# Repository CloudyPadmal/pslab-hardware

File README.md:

# pslab-hardware

This repository contains the [PSLab](https://pslab.io) hardware design files. PSLab is a tiny pocket science lab that provides an array of test and measurement instruments for doing science and engineering experiments. It can function like an oscilloscope, waveform generator, frequency counter, programmable voltage and current source and also as a data logger. The first version of hardware (v1) was developed by [Jithin B P](https://github.com/jithinbp). Later versions were developed by [Padmal](https://github.com/CloudyPadmal).

## PCB Layout
Front Side                        | Back Side
 -------------------------------- | ----------------------------------
 | 

## Pin-outs
- Find the pin-out diagram of PSLab v6 [here](docs/pin_layouts/PSLab_Pin_Layout.pdf)!

## Applications and Firmware Source Repositories

| 	|	| 	| 	| 	|
|---	|---	|---	|---	|---	|

The following software components are available:
* Firmware: https://github.com/fossasia/pslab-firmware
* Android app: https://github.com/fossasia/pslab-android
* Desktop app: https://github.com/fossasia/pslab-desktop

## Buy Device

* You can get a Pocket Science Lab device from the [FOSSASIA Shop](https://fossasia.com).
* More resellers are listed on the [PSLab website](https://pslab.io/shop/).

## Communication

* Our chat channel is on Gitter here at [PSLab](https://gitter.im/fossasia/pslab)
* Mailing List https://groups.google.com/forum/#!forum/pslab-fossasia

## Repository Structure

```
📦pslab-hardware
 ┣ 📂archives                                   # Source files for previous PSLab versions
 ┃ ┣ 📂Breakout_Boards
 ┃ ┣ 📂PSLab KiCAD
 ┃ ┣ 📂PSLab KiCAD v2
 ┃ ┗ 📂PSLab KiCAD v3
 ┣ 📂docs                                       # Supplementary material
 ┃ ┣ 📂components
 ┃ ┃ ┣ 📜BillOfMaterials.csv                    # Component list
 ┃ ┃ ┗ 📜InteractiveBoM.html                    # Interactive version of BoM
 ┃ ┣ 📂datasheets                               # PDF datasheets for components used in PSLab
 ┃ ┣ 📂drawings                                 # CAD dimension drawings
 ┃ ┣ 📂images
 ┃ ┃ ┣ 📂pslab_version_previews
 ┃ ┃ ┣ 📜 ...
 ┃ ┃ ┗ 📜PSLab_v6_top.png
 ┃ ┣ 📂pin_layouts                              # Pin labels and specifications
 ┃ ┃ ┣ 📜PSLab_Pin_Layout.pdf
 ┃ ┃ ┗ 📜PSLab_Pin_Layout.svg
 ┃ ┣ 📂position_files
 ┃ ┃ ┗ 📜PositionFile.csv                       # Pick and place information
 ┃ ┣ 📂reference                                # TeX documentation (stale)
 ┃ ┗ 📂schematics
 ┃ ┃ ┗ 📜PSLab.pdf                              # Board schematic in PDF
 ┣ 📂output
 ┃ ┣ 📂Gerber                                   # Gerber files for the current board design
 ┃ ┗ 📂Images                                   # Images of the four copper layers
 ┣ 📂print                                      # Silk screen images
 ┃ ┣ 📂Back-Side-Images
 ┃ ┗ 📜Readme.md
 ┗ 📂schematics                                 # KiCAD project files
   ┣ 📂3DModels                                 # STEP 3D models
   ┣ 📂PSLab.pretty                             # Custom library files
   ┣ 📜 ...
   ┗ 📜PSLab.pro                                # Main project file
```

## Version Information

| Version | Content | Preview |
| -------------- | ------- | ------- |
| PSLab KiCAD v1   | Original version with `SEELABLET` schematics and layout files |  |
| PSLab KiCAD v2 | Developed version with new additions (Voltage regulator, Oscillator) |  |
| PSLab KiCAD v3 | Device layout changed to Arduino Uno form factor |  |
| PSLab KiCAD v4 | Assembly optimized version with Arduino Mega form factor having components mounted only on top side |  |
| PSLab KiCAD v5 | Added socket for external bluetooth module and bottom silk screen with pin description |  |
| PSLab KiCAD v6 | Added external power input, RTC module, SD Card slot, USB type C, ESP 01 and upgraded UART and power ICs |  |

## Platform

* Microcontroller Platform : [PIC24EP256GP204](http://www.microchip.com/wwwproducts/en/PIC24EP256GP204)
* IDE: [MPLABX IDE v3.35](http://www.microchip.com/mplab/mplab-x-ide) (Supported on Linux/Windows/Mac)
* Compiler: [MPLAB® XC16 Compiler](http://www.microchip.com/mplab/compilers)
* Programming Tool: [PICkit™ 3 In-Circuit Debugger](http://www.microchip.com/Developmenttools/ProductDetails.aspx?PartNO=PG164130)

## Parts list

* [PIC24EP256GP204](http://www.microchip.com/wwwproducts/en/PIC24EP256GP204) - Microcontroller
* [MCP6S21](http://www.microchip.com/wwwproducts/en/mcp6s21) - Programmable gain amplifier
* [MCP4728](http://www.microchip.com/wwwproducts/en/mcp4728) - 4 Channel DAC
* [TC7660](http://www.microchip.com/wwwproducts/en/TC7660) - Charge Pump voltage invertor
* [TC1240A](http://www.microchip.com/wwwproducts/en/TC1240A) - Charge Pump voltage doubler
* [TL082](http://www.ti.com/product/TL082) - 2 channel Op-Amp
* [LM324](http://www.ti.com/product/LM324) - 4 channel Op-Amp
* [DS1307Z+](https://datasheets.maximintegrated.com/en/ds/DS1307.pdf) - RTC module
* [LDFM33PUR](https://www.st.com/resource/en/datasheet/ldfm.pdf) - 3.3 V regulator
* [LDL212PU50R](https://www.st.com/resource/en/datasheet/ldl212.pdf) - 5.0 V regulator
* [CP2102N-A02-GQFN24](https://www.silabs.com/documents/public/data-sheets/cp2102n-datasheet.pdf) - USB-UART bridge
* [74HC126](http://www.ti.com/product/SN74HC126) - 4 channel buffer
* [SP0503BAHTG](https://m.littelfuse.com/~/media/electronics/datasheets/tvs_diode_arrays/littelfuse_tvs_diode_array_sp05_datasheet.pdf.pdf) - ESD protector

* 0.5 A Fuse
* Assorted resistors, capacitors & diodes

Find the complete bill of materials from [this link](docs/components/BillOfMaterials.csv).

### Optional Parts

Extension slots for an ESP is available.
* [ESP8266 (ESP-01)](http://www.microchip.ua/wireless/esp01.pdf) - UART-TCP bridge

## Hardware Specs

* 3-Channel up to 2MSPS Oscilloscope. Software selectable amplification stages
* 12-bit Voltmeter with programmable gain. Input ranges from +/-10 mV to +/-16 V
* 3x 12-bit Programmable voltage sources +/-3.3 V,+/-5V,0-3 V
* 12-bit Programmable current source. 0-3.3 mA
* Supports Advanced plugins/Add-on Modules
* 4-Channel, 4 MHz Logic Analyzer
* 2x Sine/Triangular wave generators. 5 Hz to 5 KHz. Manual amplitude control for SI1
* 4x PWM generators. 15 nS resolution. Up to 8 MHz
* Capacitance Measurement. pF to uF range
* I2C, SPI and UART data buses for Accelerometer gyroscope humidity and temperature sensor modules etc

## Feature list for the acquisition and control

### Oscilloscopes

One of the main features of PSLab is the 3-channel Oscilloscope which can monitor analog inputs at maximum of 2 million samples per second. It includes controls such as triggering, and gain selection. Uses Python-Scipy for curve fitting.

### Waveform Generators

* SI1 : 5 Hz – 5 KHz arbitrary waveform generator. Manual amplitude control up to +/-3 Volts
* SI2 : 5 Hz – 5 KHz arbitrary waveform generator. Amplitude of +/-3 Volts. Attenuable via software
* SQx : There are four phase correlated PWM outputs with maximum frequency 32 MHz, 15 nano second duty cycle, and phase difference control.

### Measurement Functions

* Frequency counter tested up to 16 MHz.
* Capacitance Measurement. pF to uF range
* PSLab has several 12-bit analog inputs (function as voltmeters) with programmable gains, and maximum ranges varying from +/-5 mV to +/-16 V.

### Voltage and Current Sources

* 12-bit Constant Current source. Maximum current 3.3 mA (subject to load resistance).
* PSLab has three 12-bit Programmable voltage sources +/-3.3 V,+/-5 V,0-3 V. (PV1, PV2, PV3) controls

### Other useful tools

* 4MHz, 4-channel Logic analyzer with 15 nS resolution. Voltage and current sources
* SPI, I2C and UART outputs
* Graphical Interfaces for Oscilloscope, Logic Analyser, streaming data and several experiments developed that use a common framework which drastically reduces code required to incorporate control and plotting widgets.
* PSLab also has space for an ESP-01 module for WiFi access with access point/station mode.

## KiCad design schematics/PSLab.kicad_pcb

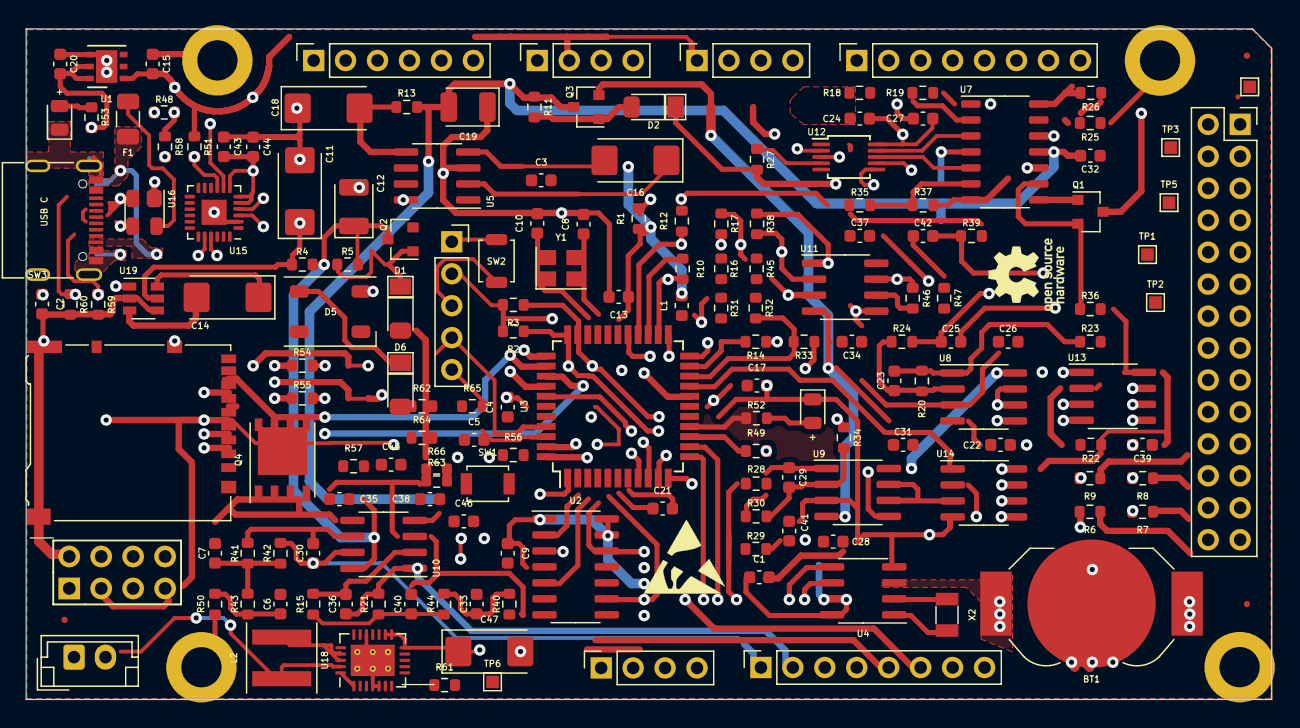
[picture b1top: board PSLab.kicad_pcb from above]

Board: 4 copper layers, 99.0 x 53.3 mm, 182 parts (0 on the bottom side), 128 nets.

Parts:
BT1: CR1225; BatteryHolder_LINX_BAT-HLD-012-SMT
BT2: CR1225; Battery_CR1225
C1, C2, C3, C4, C5, C9, C13, C17, C22, C24, C25, C26, C27, C28, C31, C32, C34, C35, C37, C38, C39, C41, C43: 0.1uF; C_0603_1608Metric
C6, C15, C21, C33, C44, C46: 10uF; C_0603_1608Metric
C7, C40: 10nF; C_0603_1608Metric
C8, C10: 33pF; C_0603_1608Metric
C11, C14, C16, C18, C47: 100uF; CP_EIA-6032-28_Kemet-C
C12, C19: 33uF; CP_EIA-3528-21_Kemet-B
C20, C42: 1uF; C_0603_1608Metric
C23, C29: 0.5pF; C_0603_1608Metric
C30, C36: 1nF; C_0603_1608Metric
C45: 2.2uF; C_0603_1608Metric
D1, D2: 6.8V; D_MiniMELF
D3: GREEN; LED_0805_2012Metric
D4: BLUE; LED_0805_2012Metric
D5: WS2812B; LED_WS2812B_PLCC4_5.0x5.0mm_P3.2mm
D6: LL4148; D_MiniMELF
F1: 1A; Fuse_1206_3216Metric
FID1, FID2, FID3: Fiducial; Fiducial_0.5mm_Mask1.5mm
J1: DoublePins; PinSocket_2x14_P2.54mm_Vertical
J2: Power Pins; PinSocket_1x08_P2.54mm_Vertical
J3: Wave Generator; PinSocket_1x08_P2.54mm_Vertical
J4, J5: I2C; PinSocket_1x04_P2.54mm_Vertical
J6: ESP01; ESP-01
J7: UART; PinSocket_1x04_P2.54mm_Vertical
J9: SPI; PinSocket_1x06_P2.54mm_Vertical
J11: Li-Ion Battery; JST_EH_B2B-EH-A_1x02_P2.50mm_Vertical
L1: 10uH; L_0603_1608Metric
L2: 2.2uH; L_Coilcraft_XAL5030
MH1, MH2, MH3, MH4: M; MountingHole_3.2mm_M3_DIN965_Pad
P1: SDCard; microSD_HC_Hirose_DM3AT-SF-PEJM5
Q1, Q3: MMBT3906; SOT-23
Q2: MMBT3904; SOT-23
Q4: Q_NMOS_DGS; PowerPAK_SO-8_Single
R1, R10, R14, R16, R17, R18, R19, R21, R22, R23, R25, R28, R29, R31, R32, R33, R35, R37, R38, R39, R42, R58: 10K; R_0603_1608Metric
R2, R3, R12, R15, R26, R41, R43, R44, R48, R52, R53, R59, R60: 5K1; R_0603_1608Metric
R4, R13, R54, R55, R56, R57: 18; R_0603_1608Metric
R5, R11, R27, R36, R47, R51: 1K; R_0603_1608Metric
R6, R7, R8, R9, R49: 200; R_0603_1608Metric
R20, R30, R40, R46, R50: 200K; R_0603_1608Metric
R24, R34, R45: 1M; R_0603_1608Metric
R61: 2K; R_0603_1608Metric
R62: 6m; R_0603_1608Metric
R63: 1690K; R_0603_1608Metric
R64: 324K; R_0603_1608Metric
R65: 178K; R_0603_1608Metric
R66: 60.4K; R_0603_1608Metric
SW1: BOOT; SW_SPST_B3U-1000P
SW2: MCLR Reset; SW_SPST_B3U-1000P
SW3: USB_C - Generic; USB_C_Receptacle_XKB_U262-16XN-4BVC11
TP1, TP2, TP3, TP5, TP6: TEST; TestPoint_Pad_1.0x1.0mm
TP4: GND; TestPoint_Pad_1.0x1.0mm
U1: LDFM33PUR; DFN-6-1EP_3x3mm_P0.95mm_EP1.7x2.6mm
U2: 74HC126; SOIC-14_3.9x8.7mm_P1.27mm
U3: PIC24EP256GP204; TQFP-44_10x10mm_P0.8mm
U4: DS1307Z+; SOIC-8_3.9x4.9mm_P1.27mm
U5: TC7660; SOIC-8_3.9x4.9mm_P1.27mm
U7: LM324; SOIC-14_3.9x8.7mm_P1.27mm
U8, U9, U10, U11: TL082; SOIC-8_3.9x4.9mm_P1.27mm
U12: MCP4728; MSOP-10_3x3mm_P0.5mm
U13, U14: MCP6S21; SOIC-8_3.9x4.9mm_P1.27mm
U15: CP2102N; QFN-24-1EP_4x4mm_P0.5mm_EP2.6x2.6mm
U16: SP0503BAHT; SOT-143
U18: LTC4040
U19: TC1240A; SOT-23-6
X2: 32.768 kHz; Crystal_SMD_3215-2Pin_3.2x1.5mm
Y1: 12 MHz; Crystal_SMD_3225-4Pin_3.2x2.5mm
Z1: Programmer; PinSocket_1x05_P2.54mm_Vertical
Z2: GND; TestPoint_Pad_1.0x1.0mm
Z3: VBUS; TestPoint_Pad_1.0x1.0mm
Z4: D+; TestPoint_Pad_1.0x1.0mm
Z5: D-; TestPoint_Pad_1.0x1.0mm
Z7: PSLab BarCode; Barcode
Z8: QR Code; Website_QR
Z10: ESD-Logo; ESD-Logo_6.6x6mm_SilkScreen
Z11: OpenHardware; OSHW-Logo_5.7x6mm_SilkScreen

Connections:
+3V3: C2.1, C4.1, C13.1, C15.2, C43.1, C44.1, J4.2, J5.1, J6.2, J6.7, J7.1, J9.6, L1.2, P1.4, R1.1, R2.2, R3.2, R51.2, U1.1, U3.28, U3.40, U15.5, U15.6, U15.7, Z1.2
+5V: C1.1, C9.1, C20.2, C47.1, D6.2, Q4.1, R48.1, R53.1, R63.1, U1.5, U1.6, U2.1, U2.4, U2.10, U2.13, U2.14, U4.8, U18.1, U18.12, U18.13, U18.14, U18.24, U19.1
+6V: C26.1, C31.1, C37.1, Q2.2, TP2.1, U8.8, U9.8, U11.8
+10V: C12.1, C27.1, C35.1, Q2.3, R4.2, R5.2, TP6.1, U7.4, U10.8
-6V: C22.1, C28.1, C34.1, Q3.2, TP3.1, U8.4, U9.4, U11.4
-10V: C19.2, C32.1, C38.1, Q3.3, R11.2, R13.2, TP5.1, U7.11, U10.4
/BATT: J11.2, L2.1, U18.23
/CAP: J1.6, R10.2, U3.24
/CC1: R60.2, SW3.A5
/CC2: R59.2, SW3.B5
/CLN: Q4.3, R62.2, U18.7
/D+: SW3.A6, SW3.B6, U15.3, U16.3, Z4.1
/D-: SW3.A7, SW3.B7, U15.4, U16.2, Z5.1
/DAC.1: U7.3, U12.9
/DAC.2: U7.5, U12.8
/DAC.4: U7.10, U12.6
/DBL: C11.1, R4.1, U5.8, U19.5
/IGATE: Q4.2, U18.15
/LA1_: R6.2, U3.8
/LA2_: R7.2, U3.9
/LA3_: R8.2, U3.10
/LA4_: R9.2, U3.11
/L_SW: C46.2, L2.2, U18.21, U18.22
/MRxD: R54.1, U15.20
/MTxD: R55.1, U15.21
/OSC_IN: C10.1, U3.30, Y1.1
/OSC_OUT: C8.1, U3.31, Y1.3
/OSC_REF: R16.1, R17.1, U8.5, U9.5
/PFI: R65.2, R66.2, U18.19
/RES: J1.4, R12.1, U3.26
/RxD: R54.2, U3.43
/SQR1_: U2.2, U3.2
/SQR2_: U2.5, U3.3
/TxD: R55.2, U3.44
/UARTReset: R51.1, U15.9
/VBusSense: R48.2, R58.2, U15.8
/VINPUT: C45.1, F1.2, R62.1, R65.1, U16.4, U18.6, U18.16
/VOL: J1.2, U3.27
/VUSBIN: F1.1, SW3.A4, SW3.A9, SW3.B4, SW3.B9, Z3.1
ACH1: C25.2, J1.20
AVSS: BT1.2, C1.2, C2.2, C3.1, C4.2, C5.1, C7.2, C8.2, C9.2, C10.2, C11.2, C12.2, C13.2, C15.1, C17.2, C18.1, C19.1, C20.1, C21.2, C22.2, C24.1, C26.2, C27.2, C28.2, C31.2, C32.2, C34.2, C35.2, C37.2, C38.2, C39.2, C40.2, C41.2, C43.2, C44.2, C45.2, C46.1, C47.2, D1.2, D2.1, D3.1, D4.1, D5.3, J1.1, J1.3, J1.5, J1.7, J1.9, J1.11, J1.13, J1.15, J1.17, J1.19, J1.21, J1.23, J1.25, J1.27, J2.1, J2.3, J2.5, J2.7, J3.3, J3.8, J4.1, J5.2, J6.1, J7.4, J9.5, J11.1, MH1.1, MH2.1, MH3.1, MH4.1, P1.6, P1.11, R17.2, R25.1, R27.1, R40.1, R45.1, R50.1, R58.1, R59.1, R60.1, R61.2, R64.1, R66.1, SW1.2, SW2.2, SW3.A1, SW3.A12, SW3.B1, SW3.B12, SW3.S1, TP4.1, U1.4, U1.7, U2.7, U3.6, U3.16, U3.29, U3.39, U4.4, U5.3, U8.3, U9.3, U10.3, U10.5, U11.5, U12.10, U13.4, U14.4, U15.2, U15.25, U16.1, U18.4, U18.5, U18.17, U18.25, U19.2, U19.4, Y1.2, Y1.4, Z1.3, Z2.1
BOOT: C5.2, SW1.1, U3.38
CH1: C25.1, J1.18, R24.2
CH1out: U3.22, U13.1
CH2: J1.16, R34.2
CH2out: U3.19, U14.1
CH3: J1.14, R45.2, U11.3
CH3.GAIN: J1.12, R38.1, U11.2
CH3out: R32.1, R33.1, U3.20
CS.CH1: U3.12, U13.5
CS.CH2: U3.13, U14.5
CS.CH3: P1.2, U3.1
FQy: J1.8, R49.2
LA1: J1.28, R6.1
LA2: J1.26, R7.1
LA3: J1.24, R8.1
LA4: J1.22, R9.1
MCLR: C3.2, R1.2, SW2.1, U3.18, Z1.1
MIC: C42.2, J1.10, R39.1
MICout: R14.1, R31.2, U3.21
unnamed: BT1.1, U4.3
unnamed: C6.2, R43.1, R50.2
unnamed: C7.1, R41.1, R42.1, R43.2
unnamed: C14.1, U19.6
unnamed: C14.2, U19.3
unnamed: C16.1, U5.2
unnamed: C16.2, U5.4
unnamed: C18.2, R13.1, U5.5
unnamed: C21.1, U3.7
unnamed: C23.1, R20.2, R23.1, U8.1
unnamed: C23.2, R20.1, R24.1, U8.2
unnamed: C29.1, R28.1, R30.1, U9.1
unnamed: C29.2, R30.2, R34.1, U9.2
unnamed: C30.2, R41.2, U10.6
unnamed: C33.2, R40.2, R44.2
unnamed: C36.2, R15.2, U10.2
unnamed: C40.1, R15.1, R21.1, R44.1
unnamed: C42.1, R47.1
unnamed: D1.1, Q2.1, R5.1
unnamed: D2.2, Q3.1, R11.1
unnamed: D3.2, R52.2
unnamed: D4.2, R53.2
unnamed: D5.1, D6.1
unnamed: Q1.1, U7.8
unnamed: Q1.2, R36.1, U7.9
unnamed: R10.1, U3.25
unnamed: R14.2, R46.2, U11.7
unnamed: R18.2, R19.2, U7.2
unnamed: R19.1, U7.1, U7.12
unnamed: R22.2, R23.2, U13.2
unnamed: R25.2, R26.2, U7.13
unnamed: R27.2, U12.4
unnamed: R28.2, R29.2, U14.2
unnamed: R33.2, R38.2, U11.1
unnamed: R35.2, R37.1, U7.6
unnamed: R46.1, R47.2, U11.6
unnamed: R49.1, U3.14
unnamed: R61.1, U18.2
unnamed: R63.2, R64.2, U18.10, U18.18
unnamed: U4.1, X2.1
unnamed: U4.2, X2.2
unnamed: U8.6, U8.7, U13.3
unnamed: U9.6, U9.7, U14.3
PCS: J2.2, Q1.3
PGC2: R56.1, U3.42, Z1.5
PGD2: R57.1, U3.41, Z1.4
PVS1: J2.8, R26.1, U7.14
PVS2: J2.6, R37.2, U7.7
PVS3: J2.4, U12.7
RGB: D5.4, U3.23
RxD2: J6.3, J7.3, R56.2
SCK: J9.4, P1.5, U3.36, U13.7, U14.7
SCL: J4.4, J5.3, R2.1, U3.33, U4.6, U12.2
SDA: J4.3, J5.4, R3.1, U3.32, U4.5, U12.3
SDI: J9.2, P1.7, U3.35
SDO: J9.3, P1.3, U3.34, U13.6, U14.6
SINE1: C30.1, J3.1, R42.2, U10.7
SINE2: C36.1, J3.2, R21.2, U10.1
SPI.CS: J9.1, U3.37
SQR1: J3.4, U2.3
SQR2: J3.5, U2.6
SQR3: J3.6, U2.11
SQR3_: C33.1, U2.12, U3.4
SQR4: J3.7, U2.8
SQR4_: C6.1, U2.9, U3.5
STAT: R52.1, U3.15
TxD2: J6.4, J7.2, R57.2
VDDA: C17.1, C24.2, C39.1, C41.1, L1.1, R12.2, R16.2, R18.1, R22.1, R29.1, R31.1, R32.2, R35.1, R36.2, R39.2, TP1.1, U3.17, U12.1, U13.8, U14.8

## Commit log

2021-05-30 chore: pull request actions
2021-05-30 chore: pull request messages
2021-06-01 chore: upload diff images to pr
2021-06-01 test
2021-06-01 chore: updated pr workflow
2021-06-01 fix: osc signal routes
2021-06-01 refactor: global track refresh
2021-06-01 upgrade: lm324 to tssop14
2021-06-01 refactor: osc placement
2021-06-02 refactor: wave generator circuit
2021-06-02 refactor: caps for esp
2021-06-02 refactor: initial routing
2021-06-02 refactor: layout update for osc parts
2021-06-03 refactor: basic routing without ground traces
2021-07-11 chore: updating board diff images
